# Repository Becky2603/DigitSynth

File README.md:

# DigitSynth

DigitSynth is a wearable MIDI controller that interacts with the Roland JD-Xi synthesiser. It allows the user to trigger chords and shape the resulting sound in real time using finger movements.

## Hardware Requirements
 
### Bill of Materials

The table below outlines the hardware components used in this project. Exact component matches are not required, and suitable alternatives will yield comparable results. However, as the software has been developed specifically for the Raspberry Pi, it is strongly recommended to retain this as the target platform.
 
| Component | Part Number | Quantity | Approx. Cost (unit)|
|---|---|---|---|
| Raspberry Pi 5 | Pi 5 4GB | 1 | £105.60 |
| Adafruit ADS1115 | 1085 | 1 | £11.18 |
| Adafruit TLC59711 | 1455 | 1 | £6.73 |
| Spectra Symbol Flex Sensor FLX| FLX-L-055-123-MP | 4 | £8.51 |
| Tactile Switch, 4.3mm | MCDTS2-1N| 4 | £0.17 |
| Kingbright L-7113IT 5mm 2V Red LED 80mcd | 56-0250 | 8 | £0.08 |
| Pisugar S Plus 5000 mAh Raspberry Pi UPS | Pisugar S Plus | 1 | £29.99 |

A MIDI-receiving device is required to complete the setup, either a hardware synthesiser or a software synthesiser running on a connected laptop. In this project, a Roland JD-Xi synthesiser was used, receiving MIDI directly from the Raspberry Pi over USB-B.

### Wiring Diagram:

## Architecture

<details>
<summary>UML class diagram</summary>

</details>

## Software Requirements

### Toolchain
Our build system is CMake, but we provide a simple top-level Makefile to make things easy. Feel free to run the `cmake` commands manually if you are so inclined. The `install-deps.sh` script will automatically install dependencies required by DigitSynth. 

## Installing
A simple install can be performed using the `.deb` package in the latest release. Download `digitsynth-aarch64.deb`, then run ```bash sudo dpkg -i digitsynth-aarch64.deb``` in your terminal after navigating to the directory into which the archive was downloaded. The standalone binary can also be found in the release.  Note that dependencies still need to be installed. 

## Building

### 1.1 Clone the Repository
 
```bash
git clone https://github.com/RTES-Group/DigitSynth.git
cd DigitSynth
```

OR 

### 1.2 Download the release
Find the latest release on the right-hand side of this page. Download either the `.tar.gz` or `.zip`. After downloading and navigating to the download directory: 

#### `zip`
```bash 
unzip DigitSynth-xx.xx.xx.zip

cd DigitSynth-xx.xx.xx
```

#### `tar.gz`
```bash 
tar -xf DigitSynth-xx.xx.xx.tar.gz

cd DigitSynth-xx.xx.xx
```

### 2. Install Dependencies

#### Dependencies

| Library | Purpose | Source |
|---|---|---|
| IIR Filter Library | Digital IIR filter design and processing | [berndporr/iir1](https://github.com/berndporr/iir1) |
| RtMidi | Real-time MIDI input/output | [thestk/rtmidi](https://github.com/thestk/rtmidi) |
| ADS1115 API | Flex sensor measurement | [berndporr/rpi_ads1115](github.com/berndporr/rpi_ads1115) |
| libgpiod | GPIO management | [ligpiod](https://libgpiod.readthedocs.io/en/latest/building.html) | 
| libasound2-dev | ALSA development headers | [libasound2-dev](https://alsa-project.org/) |

Simply run the `install-deps.sh` script:
```bash 
./install-deps.sh
```

### 3. Enable SPI and I2C on the Raspberry Pi:
SPI must be enabled before the project will run:

```bash
sudo raspi-config
# Navigate to: Interface Options → SPI → Enable
# Navigate to: Interface Options → I2C → Enable
```

### 4. Build the project:

```bash
cd application/
make
```

### 5. Run:
```bash
build/digitsynth
```

---

## Unit tests

To run unit tests: 
```bash 
make test
```
---
## User Guide

A full user guide covering button modes, controls, and MIDI mapping is available here:

 [DigitSynth User Guide](docs/HowToUse.pdf)
 
---
## Demonstration Videos

| Demo 1 | LED Mode Demo | Demo 2 |
|---|---|---|
|  |  |  |

---
## Social Media

Follow our build journey on Instagram: 

We are also awaiting a write-up on [Hackaday.com](https://hackaday.com) about our project, so keep an eye out on their blog!

---

## Contributing

See the issues tab for a list of potential contributions. In particular, we would welcome expanding support for other synths. 

---
## License

This project is licensed under the **MIT License** — see the [`LICENSE`](LICENSE) file for details.
 
You are free to use, modify, and distribute this project. We just ask that you credit the original authors.

---

## Authors & Acknowledgements

Developed by:

- **Logan Brown** — [GitHub](https://github.com/LoganBrownGU)
- **Becky Clarke** — [GitHub](https://github.com/Becky2603)
- **Dougal Harris** — [GitHub](https://github.com/DougalH1)
- **Finn McConville** — [GitHub](https://github.com/finnmcco)
- **Jamie Wedlinscky** — [GitHub](https://github.com/jwedlinscky)
  
As part of the **Real-Time Embedded Systems** module at **University of Glasgow**, *2026*.

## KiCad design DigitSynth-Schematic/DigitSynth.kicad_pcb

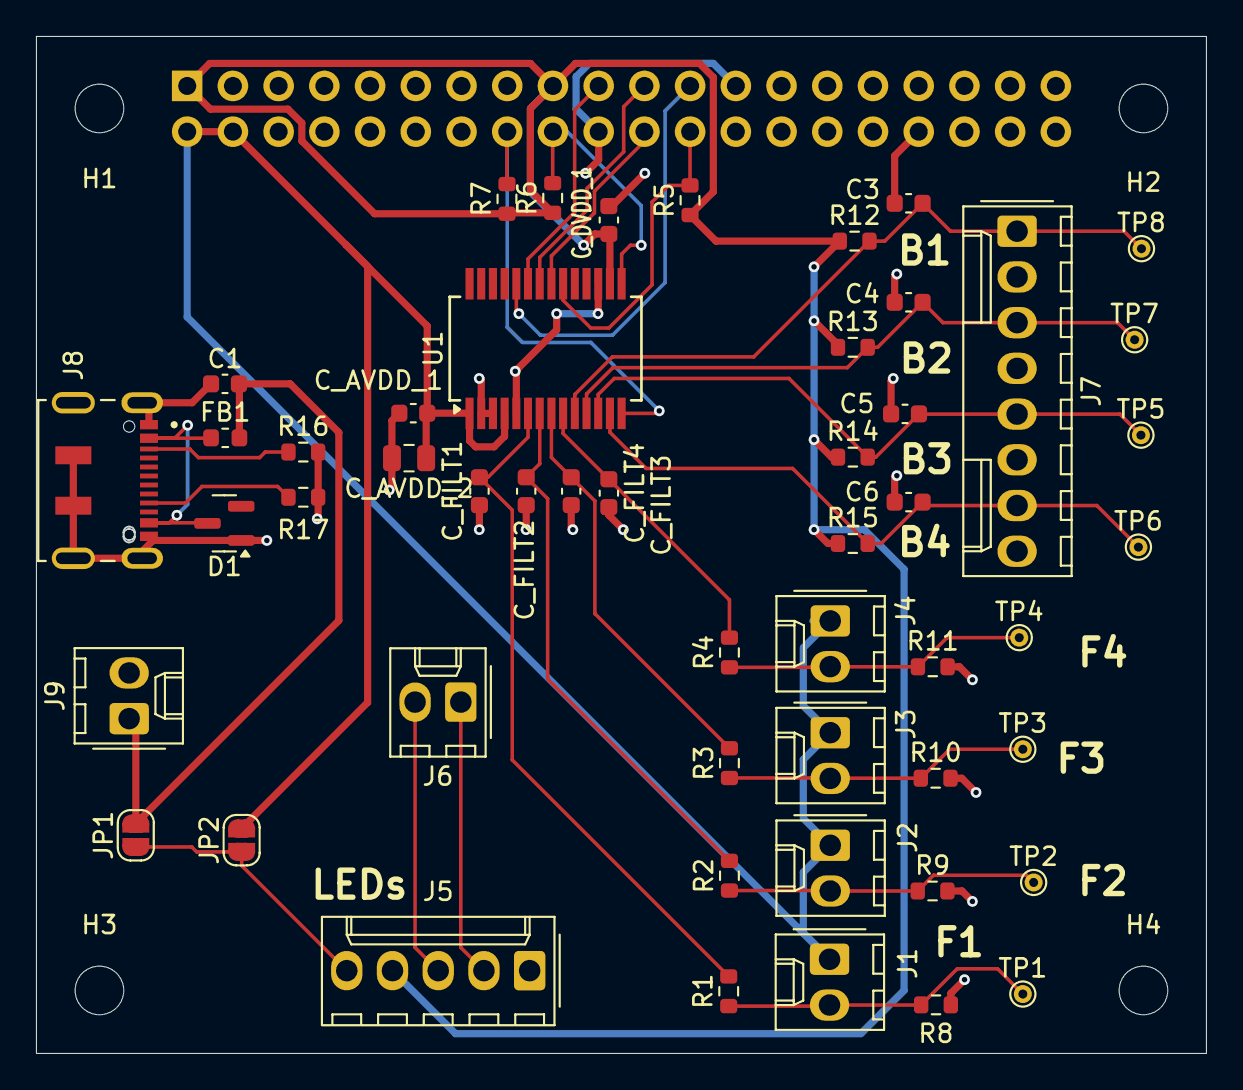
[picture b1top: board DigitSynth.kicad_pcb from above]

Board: 2 copper layers, 65.0 x 56.5 mm, 56 parts (1 on the bottom side), 29 nets.

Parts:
C1: 100nF; C_0603_1608Metric
C3, C4, C5, C6: 100n; C_0603_1608Metric
C_AVDD_1: 0.1u; C_0603_1608Metric
C_AVDD_2: 10u; C_0805_2012Metric
C_DVDD_1: 100n; C_0603_1608Metric
C_FILT1, C_FILT2, C_FILT3, C_FILT4: 0.33u; C_0603_1608Metric
D1: BZX84C5V6; SOT-23
FB1: 330Ω; L_0603_1608Metric
H1, H2, H3, H4: MountingHole; MountingHole_2.7mm_M2.5
J1, J2, J3, J4, J6, J9: Conn_01x02_Pin; Molex_KK-254_AE-6410-02A_1x02_P2.54mm_Vertical
J5: Conn_01x05_Pin; Molex_KK-254_AE-6410-05A_1x05_P2.54mm_Vertical
J7: Conn_01x08; Molex_KK-254_AE-6410-08A_1x08_P2.54mm_Vertical
J8: USB_C_Receptacle_USB2.0_JAE; JAE_DX07S016JA1R1500
JP1, JP2: Jumper_2_Open; SolderJumper-2_P1.3mm_Open_RoundedPad1.0x1.5mm
J_RPI1: THD-20-R; PinHeader_2x20_P2.54mm_Vertical
R1, R2, R3, R4: 1k; R_0603_1608Metric
R5, R6, R7, R12, R13, R14, R15: 10k; R_0603_1608Metric
R8, R9, R10, R11: 12k; R_0603_1608Metric
R16, R17: 5K1; R_0603_1608Metric
TP1, TP2, TP3, TP4, TP5, TP6, TP7, TP8: TestPoint; TestPoint_THTPad_D1.0mm_Drill0.5mm
U1: ADS1256IDBR; SSOP-28_5.3x10.2mm_P0.65mm

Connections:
+3V3_PI: C_DVDD_1.1, J5.4, J_RPI1.1, J_RPI1.17, R5.1, R6.1, R7.1, R12.1, R13.1, R14.1, R15.1, U1.16 (DVDD)
+5V_EXT: C1.1, FB1.2, J9.1, JP1.2 (B)
+5V_PI: C_AVDD_1.1, C_AVDD_2.1, J1.1, J2.1, J3.1, J4.1, JP2.2 (B), J_RPI1.2, J_RPI1.4, U1.1 (AVDD), U1.4 (VREFP)
/ADC Flex/ADC_CS: J_RPI1.24, R5.2, U1.20 (~CS)
/ADC Flex/ADC_DRDY: J_RPI1.22, U1.21 (~DRDY)
/ADC Flex/ADC_RESET: J_RPI1.18, R6.2, U1.15 (~RESET)
/ADC Flex/ADC_SYNC_PDWN: J_RPI1.16, R7.2, U1.14 (~SYNC,_~PDWN)
/ADC Flex/BTN_1: C3.1, J7.1, R12.2, TP8.1, U1.10 (AIN4)
/ADC Flex/BTN_2: C4.1, J7.3, R13.2, TP7.1, U1.11 (AIN5)
/ADC Flex/BTN_3: C5.1, J7.5, R14.2, TP5.1, U1.12 (AIN6)
/ADC Flex/BTN_4: C6.1, J7.7, R15.2, TP6.1, U1.13 (AIN7)
/ADC Flex/FLEX1_V: J1.2, R1.1, R8.1, TP1.1
/ADC Flex/FLEX2_V: J2.2, R2.1, R9.1, TP2.1
/ADC Flex/FLEX3_V: J3.2, R3.1, R10.1, TP3.1
/ADC Flex/FLEX4_V: J4.2, R4.1, R11.1, TP4.1
/ADC Flex/SPI0_MISO: J_RPI1.21, U1.22 (DOUT)
/ADC Flex/SPI0_MOSI: J_RPI1.19, U1.23 (DIN)
/ADC Flex/SPI0_SCLK: J_RPI1.23, U1.24 (SCLK)
GND: C1.2, C3.2, C4.2, C5.2, C6.2, C_AVDD_1.2, C_AVDD_2.2, C_DVDD_1.2, C_FILT1.2, C_FILT2.2, C_FILT3.2, C_FILT4.2, D1.1 (A), J5.1, J7.2, J7.4, J7.6, J7.8, J8.A1 (GND), J8.A12 (GND), J8.S1 (SHIELD), J9.2, J_RPI1.6, J_RPI1.9, J_RPI1.14, J_RPI1.20, J_RPI1.25, J_RPI1.30, J_RPI1.34, J_RPI1.39, R8.2, R9.2, R10.2, R11.2, R16.2, R17.2, U1.2 (AGND), U1.3 (VREFN), U1.5 (AINCOM), U1.17 (DGND)
unnamed: D1.3 (K), FB1.1, J8.A4 (VBUS), J8.B4 (VBUS)
unnamed: J5.5, JP1.1 (A), JP2.1 (A)
unnamed: J8.A5 (CC1), R16.1
unnamed: J8.B5 (CC2), R17.1
unnamed: C_FILT1.1, R1.2, U1.6 (AIN0)
unnamed: C_FILT2.1, R2.2, U1.7 (AIN1)
unnamed: C_FILT3.1, R3.2, U1.8 (AIN2)
unnamed: C_FILT4.1, R4.2, U1.9 (AIN3)
SPI2_CLK: J5.2, J6.1
SPI2_DATA: J5.3, J6.2

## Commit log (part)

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2026-01-27 Added README
2026-01-27 Actual README
2026-01-27 Add DONOTREAD.txt with initial content
2026-02-04 Added research directory
2026-02-04 ADC research
2026-02-20 Basic UML diagram of ADC software architecture
2026-02-20 Application directory
2026-02-20 Updated README with build instructions
2026-02-20 Copyable code blocks
2026-02-20 Build directory
2026-02-20 Improved CMakeLists
2026-02-20 Release build option
2026-02-25 Update flex-sensor.md
    Added extra details for specific flex sensor part information.
2026-02-25 User stories
2026-02-25 Hinge design - male and female as wel as config update for paramters
2026-02-25 main.scad and middleSection.scad creation for full fileset creation
2026-03-03 Add detailed software architecture to README
    Expanded the design document to include detailed software architecture in pseudocode , setup instructions, and descriptions of analogue sensors, digital buttons, event processing, and shutdown proced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
2026-03-03 Trying to get template Publisher/Subscriber working
2026-03-03 Removed subscriber/published for now
    Will try `std::function` instead, may return to this later
2026-03-03 Inital OpenSCAD deign prototype
2026-03-03 Create midi-thread-scope
    MIDI encoding thread documentation.
    Defines scope and responsibility of this section of the project, with inputs (button + flex sensor data), processing steps and outputs (USB MIDI messages).
2026-03-06 Delete midi-thread-scope.md
    document no longer relevant and replaced by a clearer specification
2026-03-06 Delete midi-thread-scope.md
    replaced with a clearer spec
2026-03-06 Rename synth-logic-rules to synth-logic-rules.md
    .md
2026-03-07 Add files via upload
    First review of schematic with noted issues and suggested improvements
2026-03-08 Modifying LEDDriver.h for 10-LED brightness input
2026-03-08 Simplifying the header file for single chip application. writeSPI set to private to avoid duplication and removed numchips as we are no longer daisy chaining
2026-03-08 creation of cpp skeleton for LED pwm driver. includes constants declartaion and function defintions
2026-03-11 Added `sys/types.h`
2026-03-11 Basic test for spi
2026-03-12 removed power schematic sheet as RPI5 has decoupling capacitors; fixed component value errors; buttons removed from RPI5 sheet and added to ADC analog inputs; LED_VPLUS power line removed and replace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
2026-03-12 Add MIDI Driver header for CC output functionality
    This header file implements a MIDI output driver using the RtMidi library, allowing for sending MIDI Control Change messages. It includes class definitions, methods for sending messages, and example 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
2026-03-12 updated schematic for PCB design
2026-03-12 Rename midi_driver.hpp to midi_driver.h
    renamed for consistency with other header files
2026-03-15 Register info
2026-03-17 Careful with ownership
2026-03-17 Fixes for memory issues with smart pointers
    Using raw pointers for now, should fix later
2026-03-17 hello world for GPIO init and LED toggling.
    Stub for LED driver implementation
2026-03-18 Fixed bit order bugs and the like
2026-03-18 Fixed cmake and tlc include
2026-03-24 Delete design/README.md
    its wrong
2026-03-24 Working Led control for R0,G0,B0. PWM and blinking demonstrated.
    Working now on implmentation into distinct class for realtime operation
2026-03-24 Removed wiringPi
2026-03-24 implement worker, update, buildPacket, shiftOut and gamma
2026-03-25 ripple pattern with 3 simultaneous fingers
2026-03-25 Very poor but functional gpio callback
2026-03-25 Tidying up
2026-03-29 add SynthController interface and shells for callbacks
2026-03-29 ignore .DS_Store in application
2026-04-01 Failed attempts to get itw working
2026-04-02 commiting to merge with gpio-driver
2026-04-02 Replace lgpio handle and pipe with condvar synchronisation
2026-04-02 Replace -llgpio with -lgpiodcxx, remove duplicated source blocks
2026-04-02 Tidying up includes
2026-04-02 Replace LEDFrame struct with std::array<Brightness, NUM_LEDS>
    Remove LEDFrame in favour of a Channels type alias defined directly on
    the class.
2026-04-04 Scaler class to scale normalised flex sensor float values to MIDI integer range, with a test included
2026-04-04 assert test for mapper class
2026-04-05 Chord manager class for synth logic
2026-04-05 test for chord manager class
2026-04-06 added event handling for simultaneous button presses in synth logic layer
2026-04-07 Add FlexDSP header for digital signal processing
    Implement FlexDSP class for lowpass iir filtering with adjustable cutoff and callback registration.
2026-04-07 FlexDSP.cpp for dsp - filtering flex sensor data
    Implements a lowpass IIR with adjustable cutoff to smooth out sensor data noise.
2026-04-07 Doxygen working closes #15
2026-04-07 main updated to run ripple test
2026-04-08 Updated patterns to be threadsafe and allign with guidance
2026-04-08 test for TLC added static unit tests for toGS and FRAME_TO_GS
2026-04-08 Compiles
2026-04-08 Make rule to update docs on web server
2026-04-08 test for TLC adding concurrency test for update() thread safety
2026-04-08 Basic integration of LEDs and flex
2026-04-08 Add midi-driver.cpp
2026-04-10 Download tarball instead of cloning git
2026-04-10 Fixed cxx bindings flag
2026-04-10 cd into repo
2026-04-10 Trying with aarch
2026-04-10 Fixed syntax error (yikes)
2026-04-10 Added version to package
    Fixed spelling error
2026-04-10 CI builds from main
    Renamed c-cpp.yml in preparation for two separate pipelines
2026-04-13 Documented button driver
2026-04-13 Doc'd flex sensor
2026-04-13 Added new button callback types to `button-driver.cpp` (#54)
2026-04-13 Removed `AdcCallback` as is unused (#54)
2026-04-13 Separate log archive step
2026-04-13 Update rtmidi include file
2026-04-13 unit test for updated flex sensor handling
2026-04-13 Added synth logic combined test to tests
2026-04-13 Fix GitHub link formatting for Logan Brown
2026-04-13 MIT License for open-source usage
2026-04-13 Include license information in README
    Add license section to README with MIT License details.
2026-04-13 fix flex sensor test issue
2026-04-13 Update feature description for MIDI synthesizer
2026-04-14 Poor attempt
2026-04-14 Update midi_test port
    Changed open port from 0 to 1
2026-04-14 Update midi-driver with synth-logic callback
    Removed midi-driver wrapper methods and updated midi-driver files with MidiCallback
2026-04-14 fix pattern issue caused by double button press
2026-04-15 Add hardware requirements section to README
    Added hardware requirements and bill of materials for the project.
2026-04-15 Revise bill of materials for clarity and accuracy
    Updated the bill of materials to clarify cost per unit and corrected quantities.
2026-04-15 Correct spelling and add LED responsiveness feature
    Updated spelling of 'synthesizer' to 'synthesiser' and added a feature for responsive LEDs.
2026-04-15 Update README with software requirements and setup
    Added software requirements and installation instructions for dependencies.
2026-04-15 Rename Photo from Becky.jpg to circuit-diagram.jpg
2026-04-15 Rename circuit-diagram.jpg to wiring-diagram.jpg
2026-04-15 Update wiring diagram image in README
2026-04-15 update CMake lists
2026-04-15 Update README with SPI enabling instructions
    Added instructions to enable SPI in README.
2026-04-15 Add ADS1115 Raspberry Pi Library to README
2026-04-15 update chord manager class
2026-04-15 Added install dependencies script
    Needs to be tested on fresh Pi.
    Needs to be tested and used in CI.
2026-04-16 Removed erroring unit tests temporarily for the sake of a working pipeline
2026-04-16 Fixed CI pipeline name
2026-04-16 Unit tests workflow
2026-04-16 Make sure LD path is set
2026-04-16 No ldconfig?
2026-04-16 Change filter order from 2 to 4 in FlexDSP
2026-04-16 Added back other tests
2026-04-16 Giving up on unit tests in CI
2026-04-16 Change flexSensor callback to flexDSP callback
2026-04-16 Removed unit tests from workflow
2026-04-16 LFO manager class unit test
2026-04-16 Change heading level for Contributing section
2026-04-16 Fixed path to tests
2026-04-16 Removed test log
2026-04-16 add LED controller class in synth logic layer
2026-04-16 move LED controller header to correct folder
2026-04-17 GPIO unit test
2026-04-17 Removed `AdcData` as it is unused.
2026-04-17 Moved `Brightness` into tlc driver class
    (#54)
2026-04-17 Moved `DoneCallback` to patterns class
    (#54)
2026-04-17 Removed types.h (#54)
2026-04-17 update LedController to use dependency injection via ITLC59711 and Pattern interfaces
2026-04-17 unit test for LedController class
2026-04-17 button and flex sensor handling for SynthController class
2026-04-17 Fixed issue with delted copy constructors and interfaces
2026-04-17 Added MidiDriver to SynthController
2026-04-17 Added midi initialisation
2026-04-18 Fixed switch
2026-04-18 added in Led namespace to allow us to map fingers to LED value
2026-04-18 patterns.cpp now gets LED number value from the class that sets it rather than hard coding in the class itsself
2026-04-18 suppress unused parameter warnings for lfoEnabled and shape
2026-04-18 Added alsa to apt install
2026-04-18 Adjustd flex sensor ranging
2026-04-18 Fixed issue with flex data being duplicated
2026-04-18 Fixed LED mappings
    Dummy logan
2026-04-18 A bit of ducmentation
    (#83)
2026-04-18 Merged proper
2026-04-18 fix error in chord switch logic that was preventing transition to new chords
2026-04-18 Turn off notes in destructor
2026-04-19 Re-added all buttons callback
2026-04-19 rename ITLC59711 interface class to ILedDriver
2026-04-19 use ILedDriver interface throughout the project
2026-04-19 fix bugs related to Led Driver interface
2026-04-19 fix LedController constructor mismatch
2026-04-19 Removed superfluous unit tests
    Closes #78
2026-04-19 remove unneeded function from patterns.cpp
2026-04-19 rewrite ChordManager class unit test to use updated chord voicings
2026-04-19 Added channel segregation test
2026-04-19 Show test log with `make test`
2026-04-19 Stops when all buttons pressed
    Closes #108
2026-04-19 Re-added `control.in` after accidental deletion
2026-04-19 Updating TLC to take `unique_ptr`
2026-04-20 Add comments to midi-driver class
2026-04-20 rewrite synth logic classes to better obey open/closed principle
2026-04-20 Add ILEDPattern interface and led_pattern namespace
2026-04-20 Update LedController.cpp with led_pattern interface
2026-04-20 Update patterns.cpp with led_pattern namespace
2026-04-20 Fixed integrated_test
    Was creating a new instance of classes rather than using pointer to
    already-created instance.
2026-04-20 Builds and passes tests
2026-04-20 Rename install-deps.sh to application/install-deps.sh
2026-04-20 Rename application/install-deps.sh to install-deps.sh
2026-04-20 Uodated workflows
2026-04-20 Still can't find libgpiod on runner. Removed unit tests from workflow.
2026-04-20 Added automatic release to workflow.
2026-04-20 Separated docs build (#129)
2026-04-20 Added docs build to workflow
2026-04-20 Setup threading and waiting for flexsensor
    Exits cleanly
2026-04-20 flex sensor test passes
2026-04-20 Patterns.h updated to include relevant doxygen commentation
2026-04-20 Chord manager updated with doxygen comments
2026-04-20 main updated to reflect changes in the way that TLC class is inititialised with SPI pins instead of bit bang approach
2026-04-20 Rejigging
2026-04-20 add detailed Doxygen for IPattern and PatternRipple
2026-04-20 added Doxygen for TLC59711 header file
2026-04-20 Doxygen comments for MessageBuilder class
2026-04-20 Update UML diagram
    Increased zoom
2026-04-20 Fixed merge issues
2026-04-20 It works! Closes #139
2026-04-20 updated cmake ot reflect refactored naming schemes
2026-04-20 Removed logs
2026-04-20 Removed the vestigial callback
2026-04-20 Revise README with user guide and social media links
    Updated user guide and added links to documentation and social media.
2026-04-20 Document resistor selection and voltage divider for flex sensors
    Added detailed explanation of resistor selection and voltage divider calculations for flex sensors, including operating ranges and ADC considerations.
2026-04-20 pp's in main
